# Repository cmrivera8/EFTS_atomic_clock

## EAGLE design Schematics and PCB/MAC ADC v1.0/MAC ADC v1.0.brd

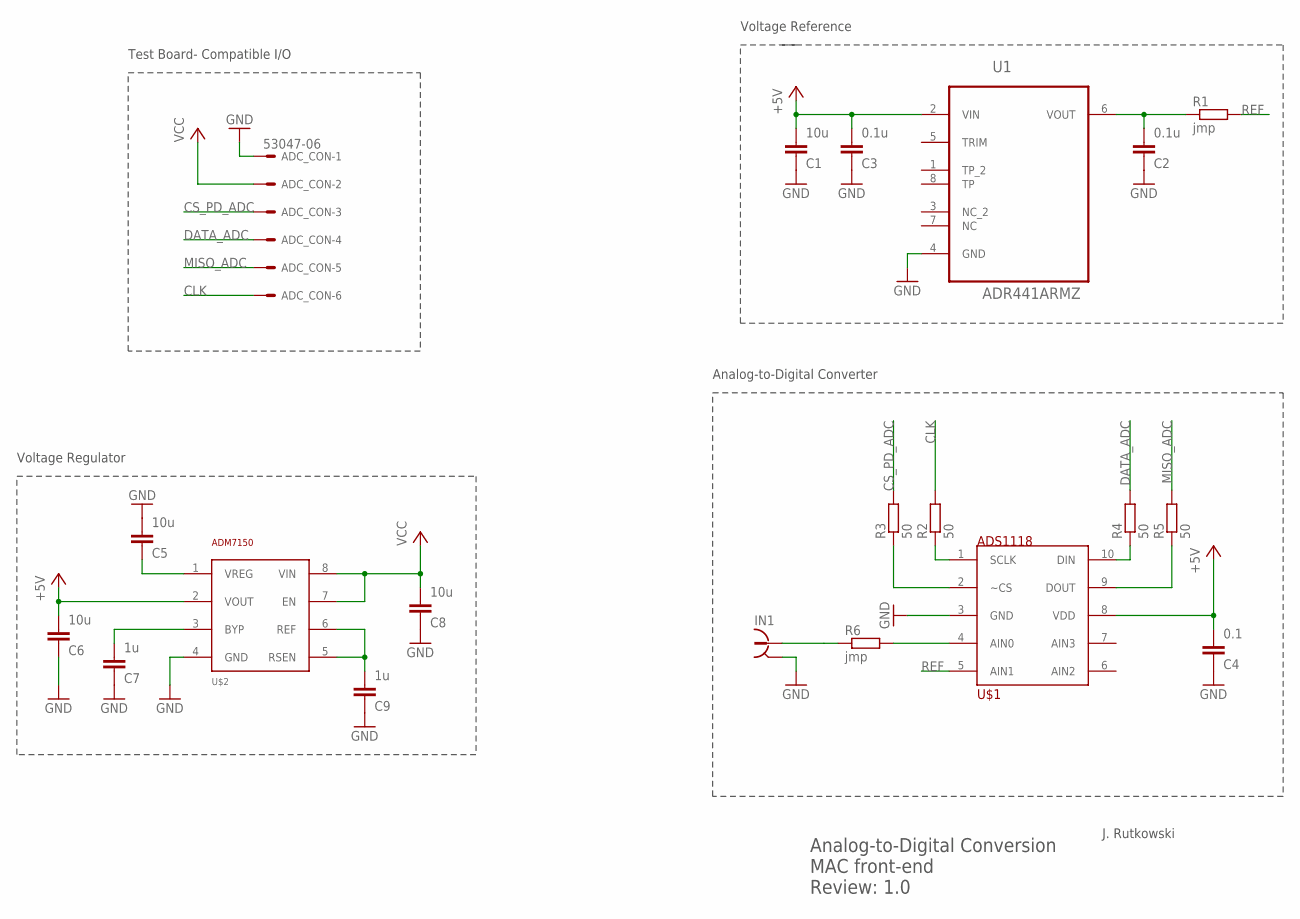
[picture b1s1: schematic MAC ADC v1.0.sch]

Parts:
ADC_CON: 53047-06
C1, C5, C6, C8: 10u; C0603K
C2, C3: 0.1u; C0603K
C4: 0.1; C0603K
C7, C9: 1u; C0603K
IN1: 734120110
R1, R6: jmp; R0603
R2, R3, R4, R5: 50; R0603
U1: ADR441ARMZ; SOP65P490X110-8N
U$1: ADS1118IDGSR; SOP50P490X110-10N
U$2: ADM7150; SO8

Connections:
+5V: C1.1, C3.1, C4.1, C6.1, U1.2 (VIN), U$1.8 (VDD), U$2.2 (VOUT)
CLK: ADC_CON.6, R2.2
CS_PD_ADC: ADC_CON.3, R3.2
DATA_ADC: ADC_CON.4, R4.2
GND: ADC_CON.1, C1.2, C2.2, C3.2, C4.2, C5.1, C6.2, C7.2, C8.2, C9.2, IN1.S@1 (2), IN1.S@2 (2), IN1.S@3 (2), U1.4 (GND), U$1.3 (GND), U$2.4 (GND)
MISO_ADC: ADC_CON.5, R5.2
unnamed: C9.1, U$2.5 (RSEN), U$2.6 (REF)
unnamed: C2.1, R1.1, U1.6 (VOUT)
unnamed: R2.1, U$1.1 (SCLK)
unnamed: C7.1, U$2.3 (BYP)
unnamed: R3.1, U$1.2 (~CS)
unnamed: C5.2, U$2.1 (VREG)
unnamed: R4.1, U$1.10 (DIN)
unnamed: R5.1, U$1.9 (DOUT)
unnamed: R6.2, U$1.4 (AIN0)
unnamed: IN1.1, R6.1
REF: R1.2, U$1.5 (AIN1)
VCC: ADC_CON.2, C8.1, U$2.7 (EN), U$2.8 (VIN)

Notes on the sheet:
Analog-to-Digital Conversion MAC front-end Review: 1.0
Voltage Reference
Analog-to-Digital Converter
Voltage Regulator
Test Board- Compatible I/O
J. Rutkowski

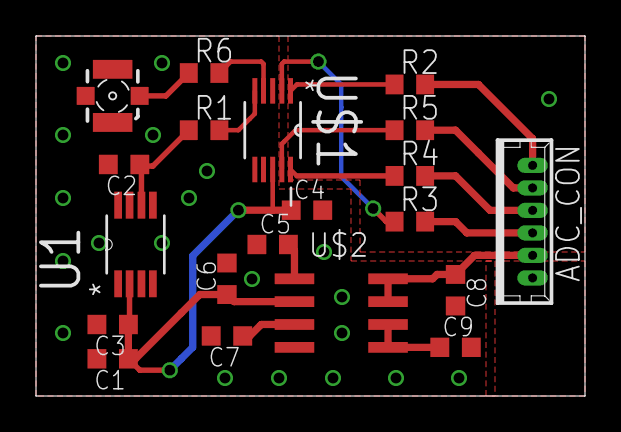
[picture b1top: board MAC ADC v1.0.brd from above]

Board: 2 copper layers, 30.5 x 20.0 mm, 20 parts (0 on the bottom side), 18 nets.

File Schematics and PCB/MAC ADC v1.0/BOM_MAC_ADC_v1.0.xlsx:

Bill of Materials
Assembly Name: | MAC ADC
Revision: | 1.0
Date: | 42632
Part Name | Value | Package | Description | Manufacturer | MPN | Ref. Farnell | Quantity | Approx. Unit Price | Stock
C1, C5, C6, C8 | 10 u | 0603 | Condensateur céramique multicouche CMS, 25 V, ± 20%, X5R | MURATA | ZRB18AR61E106ME01L | 2469398 | 4 | 0.254 | ok
C2, C3, C4 | 0,1 u | 0603 | Condensateur céramique multicouche CMS, 0.1 µF, 50 V, ± 10%, X7R | WALSIN | 0603B104K500CT | 2496834 | 3 | 1.2500000000000001E-2 | ok
C7, C9 | 1 u | 0603 | Condensateur céramique multicouche CMS, 1 µF, 6.3 V, ± 10%, X5R | MURATA | GRM188R60J105KA01D | 9527699 | 2 | 2.5100000000000001E-2 | ok
R1, R6 | 0 | - | Jumper, not mounted | - | - | - | 2 | - | -
E2, R3, R4, R5 | 49.9 | 0603 | Résistance à puce CMS, Couche épaisse, 49.9 ohm, 50 V, 63 mW, ± 1% | MULTICOMP | MC0063W0603149R9 | 1170658 | 4 | 1.1999999999999999E-3 | ok
ADC_CON | - | - | Connector, solder | - | - | - | 1 | - | -
IN1 | - | U.FL | Connecteur coaxial / RF, Coaxial RF, Jack droit, Montage en surface vertical, 5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 | MOLEX | 73412-0110 | 1340200 | 3 | 0.78400000000000003 | ok
U$1 | - | MSOP-10 | Convertisseur analogique vers numérique, 16 bit, 860 Ech/s, Simple, 2 V, 5 V | TEXAS INSTRUMENTS | ADS1118IDGSR | 1947871 | 1 | 6.02 | ok
U$2 | - | SOIC-8 | Régulateur LDO Tension fixe, 4.5V à 16V, 600mV Dropout, 5Vout, 800mAout | ANALOG DEVICES | ADM7150ARDZ-5.0 | 2377358 | 1 | 7.37 | ok
U1 | - | MSOP-8 | Référence de tension, Ultra faible bruit, Série - Fixe, Série ADR441, 2.5V | ANALOG DEVICES | ADR441ARMZ | 1274160 | 1 | 5.7 | ok
